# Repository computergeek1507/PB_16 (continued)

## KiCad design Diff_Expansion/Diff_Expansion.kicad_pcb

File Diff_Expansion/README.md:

# Copyright and Disclaimer
Copyright: Scott Hanson

This documentation describes Open Hardware and is licensed under the CERN Open Hardware License Version 2 - Strongly Reciprocal. (CERN-OHL-S)

You may redistribute and modify this documentation under the terms of the CERN OHL-S-v2 (https://ohwr.org/cern_ohl_s_v2.txt). This documentation is distributed WITHOUT ANY EXPRESS OR IMPLIED WARRANTY, INCLUDING OF MERCHANTABILITY, SATISFACTORY QUALITY AND FITNESS FOR A PARTICULAR PURPOSE. Please see the CERN OHL v2-S for applicable conditions

**Under CERN OHL-S-v2, derivative work must be publicly released as defined in subsection 3.3**

# Diff Expansion

The Diff Expansion is a four port Differental Reciever output boardfor the PB16. It works with Smart and Dumb Differental Recievers. All the design files are open source and available on github.

To order, upload the "GERBER-Diff_Expansion.zip" file in the "jlcpcb\gerber" folder to jlcpcb.com.

## [Part BOM](https://github.com/computergeek1507/PB_16/raw/master/Diff_Expansion/Diff_Expansion_BOM.ods)

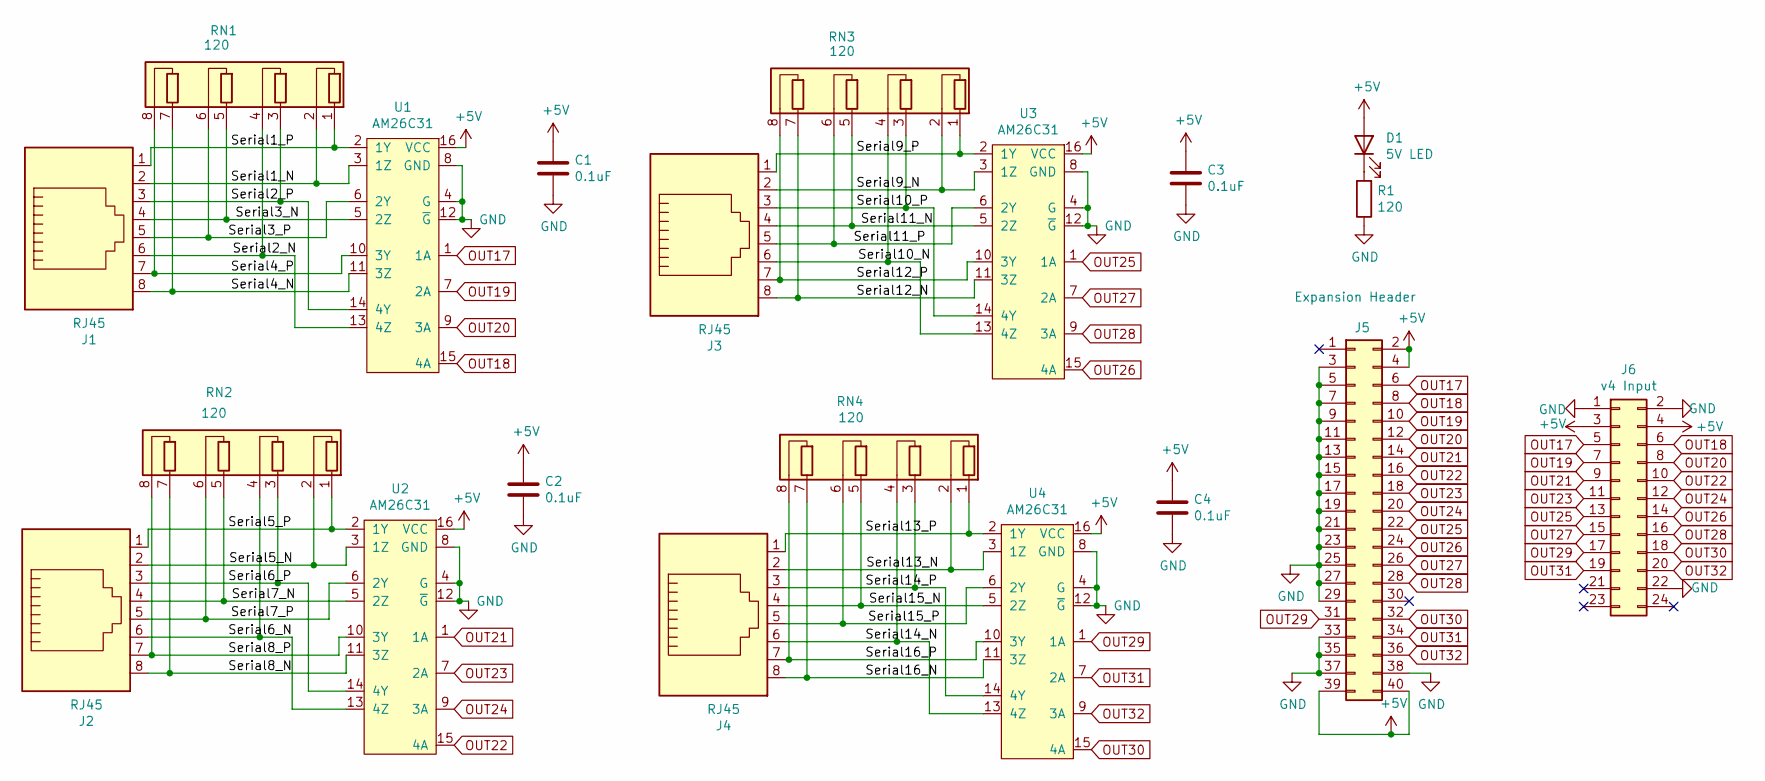
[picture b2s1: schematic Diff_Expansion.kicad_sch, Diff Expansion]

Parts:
C1, C2, C3, C4: 0.1uF; C_Rect_L7.0mm_W2.0mm_P5.00mm; MPN SR215C104KARTR1; Digi-Key_PN 478-7336-1-ND
D1: 5V LED; LED_D3.0mm_Clear; MPN WP3A8GD; Digi-Key_PN 754-1217-ND
J1, J2, J3, J4: RJ45; RJ45_Amphenol_54602-x08_Horizontal; MPN A-2014-2-4-R; Digi-Key_PN AE10392-ND
J5: Expansion Header; IDC-Header_2x20_P2.54mm_Vertical; MPN SBH11-PBPC-D20-ST-BK; Digi-Key_PN S9175-ND
J6: v4 Input; OST_302-S241; MPN 302-S241; Digi-Key_PN ED10525-ND
R1: 120; R_Axial_DIN0207_L6.3mm_D2.5mm_P7.62mm_Horizontal; MPN CF14JT120R; Digi-Key_PN CF14JT120RCT-ND
RN1, RN2, RN3, RN4: 120; R_Array_SIP8; MPN 4608X-102-121LF; Digi-Key_PN 4608X-2-121LF-ND
U1, U2, U3, U4: AM26C31; DIP-16_W7.62mm; MPN AM26C31IN; Farnell 4975637

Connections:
+5V: C1.1, C2.1, C3.1, C4.1, D1.2 (A), J5.2, J5.4, J5.39, J5.40, J6.3, J6.4, U1.16 (VCC), U2.16 (VCC), U3.16 (VCC), U4.16 (VCC)
/Serial1_N: J1.2, RN1.2 (R1.2), U1.3 (1Z)
/Serial1_P: J1.1, RN1.1 (R1.1), U1.2 (1Y)
/Serial2_N: J1.6, RN1.4 (R2.2), U1.13 (4Z)
/Serial2_P: J1.3, RN1.3 (R2.1), U1.14 (4Y)
/Serial3_N: J1.4, RN1.5 (R3.1), U1.5 (2Z)
/Serial3_P: J1.5, RN1.6 (R3.2), U1.6 (2Y)
/Serial4_N: J1.8, RN1.7 (R4.1), U1.11 (3Z)
/Serial4_P: J1.7, RN1.8 (R4.2), U1.10 (3Y)
/Serial5_N: J2.2, RN2.2 (R1.2), U2.3 (1Z)
/Serial5_P: J2.1, RN2.1 (R1.1), U2.2 (1Y)
/Serial6_N: J2.6, RN2.4 (R2.2), U2.13 (4Z)
/Serial6_P: J2.3, RN2.3 (R2.1), U2.14 (4Y)
/Serial7_N: J2.4, RN2.5 (R3.1), U2.5 (2Z)
/Serial7_P: J2.5, RN2.6 (R3.2), U2.6 (2Y)
/Serial8_N: J2.8, RN2.7 (R4.1), U2.11 (3Z)
/Serial8_P: J2.7, RN2.8 (R4.2), U2.10 (3Y)
/Serial9_N: J3.2, RN3.2 (R1.2), U3.3 (1Z)
/Serial9_P: J3.1, RN3.1 (R1.1), U3.2 (1Y)
/Serial10_N: J3.6, RN3.4 (R2.2), U3.13 (4Z)
/Serial10_P: J3.3, RN3.3 (R2.1), U3.14 (4Y)
/Serial11_N: J3.4, RN3.5 (R3.1), U3.5 (2Z)
/Serial11_P: J3.5, RN3.6 (R3.2), U3.6 (2Y)
/Serial12_N: J3.8, RN3.7 (R4.1), U3.11 (3Z)
/Serial12_P: J3.7, RN3.8 (R4.2), U3.10 (3Y)
/Serial13_N: J4.2, RN4.2 (R1.2), U4.3 (1Z)
/Serial13_P: J4.1, RN4.1 (R1.1), U4.2 (1Y)
/Serial14_N: J4.6, RN4.4 (R2.2), U4.13 (4Z)
/Serial14_P: J4.3, RN4.3 (R2.1), U4.14 (4Y)
/Serial15_N: J4.4, RN4.5 (R3.1), U4.5 (2Z)
/Serial15_P: J4.5, RN4.6 (R3.2), U4.6 (2Y)
/Serial16_N: J4.8, RN4.7 (R4.1), U4.11 (3Z)
/Serial16_P: J4.7, RN4.8 (R4.2), U4.10 (3Y)
GND: C1.2, C2.2, C3.2, C4.2, J5.3, J5.5, J5.7, J5.9, J5.11, J5.13, J5.15, J5.17, J5.19, J5.21, J5.23, J5.25, J5.27, J5.29, J5.33, J5.35, J5.37, J5.38, J6.1, J6.2, J6.22, R1.1, U1.4 (G), U1.8 (GND), U1.12 (~G), U2.4 (G), U2.8 (GND), U2.12 (~G), U3.4 (G), U3.8 (GND), U3.12 (~G), U4.4 (G), U4.8 (GND), U4.12 (~G)
unnamed: D1.1 (K), R1.2
OUT17: J5.6, J6.5, U1.1 (1A)
OUT18: J5.8, J6.6, U1.15 (4A)
OUT19: J5.10, J6.7, U1.7 (2A)
OUT20: J5.12, J6.8, U1.9 (3A)
OUT21: J5.14, J6.9, U2.1 (1A)
OUT22: J5.16, J6.10, U2.15 (4A)
OUT23: J5.18, J6.11, U2.7 (2A)
OUT24: J5.20, J6.12, U2.9 (3A)
OUT25: J5.22, J6.13, U3.1 (1A)
OUT26: J5.24, J6.14, U3.15 (4A)
OUT27: J5.26, J6.15, U3.7 (2A)
OUT28: J5.28, J6.16, U3.9 (3A)
OUT29: J5.31, J6.17, U4.1 (1A)
OUT30: J5.32, J6.18, U4.15 (4A)
OUT31: J5.34, J6.19, U4.7 (2A)
OUT32: J5.36, J6.20, U4.9 (3A)

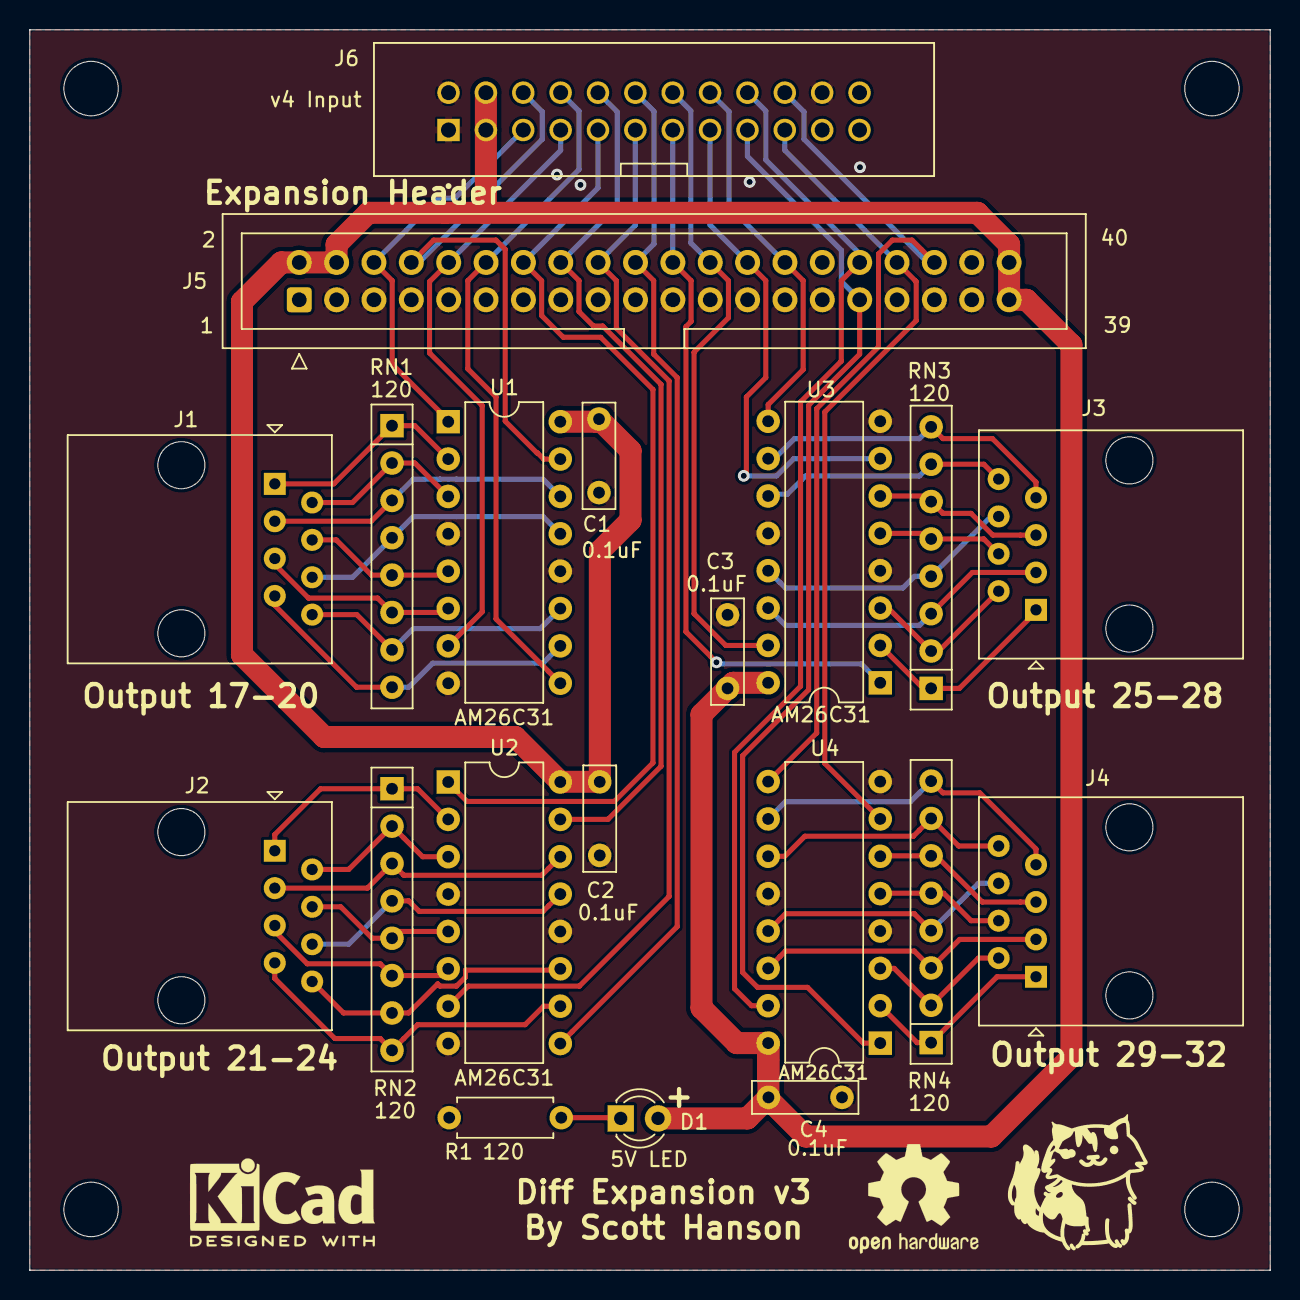
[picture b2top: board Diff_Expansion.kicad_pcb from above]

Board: 2 copper layers, 84.3 x 84.3 mm, 20 parts (0 on the bottom side), 51 nets.

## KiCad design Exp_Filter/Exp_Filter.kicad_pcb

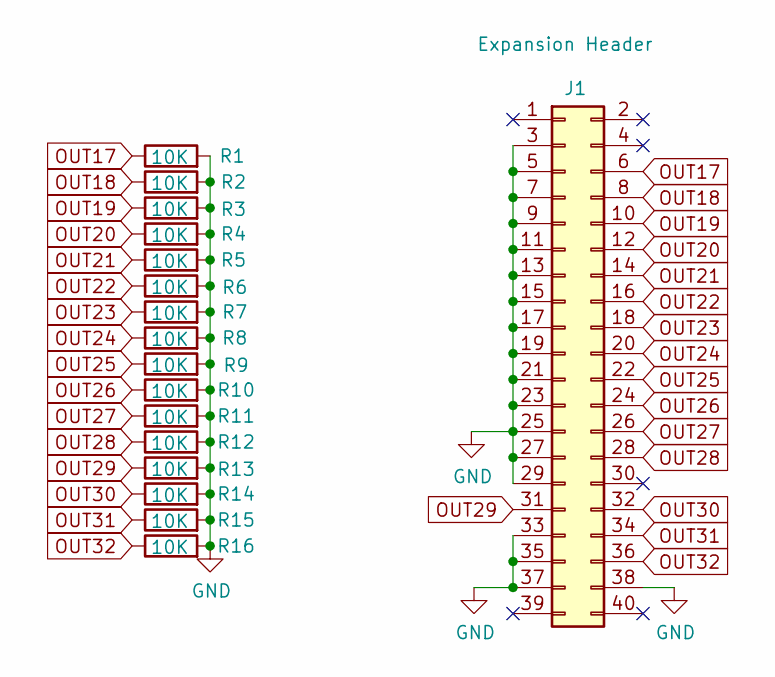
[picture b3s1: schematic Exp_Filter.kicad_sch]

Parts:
J1: Expansion Header; PinSocket_2x20_P2.54mm_Vertical; MPN SFH11-PBPC-D20-ST-BK; Digi-Key_PN S9200-ND
R1, R2, R3, R4, R5, R6, R7, R8, R9, R10, R11, R12, R13, R14, R15, R16: 10K; R_0603_1608Metric_Pad0.98x0.95mm_HandSolder; MPN RC0603FR-0710KL; Digi-Key_PN 311-10.0KHRCT-ND

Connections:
GND: J1.3, J1.5, J1.7, J1.9, J1.11, J1.13, J1.15, J1.17, J1.19, J1.21, J1.23, J1.25, J1.27, J1.29, J1.33, J1.35, J1.37, J1.38, R1.2, R2.2, R3.2, R4.2, R5.2, R6.2, R7.2, R8.2, R9.2, R10.2, R11.2, R12.2, R13.2, R14.2, R15.2, R16.2
OUT17: J1.6, R1.1
OUT18: J1.8, R2.1
OUT19: J1.10, R3.1
OUT20: J1.12, R4.1
OUT21: J1.14, R5.1
OUT22: J1.16, R6.1
OUT23: J1.18, R7.1
OUT24: J1.20, R8.1
OUT25: J1.22, R9.1
OUT26: J1.24, R10.1
OUT27: J1.26, R11.1
OUT28: J1.28, R12.1
OUT29: J1.31, R13.1
OUT30: J1.32, R14.1
OUT31: J1.34, R15.1
OUT32: J1.36, R16.1

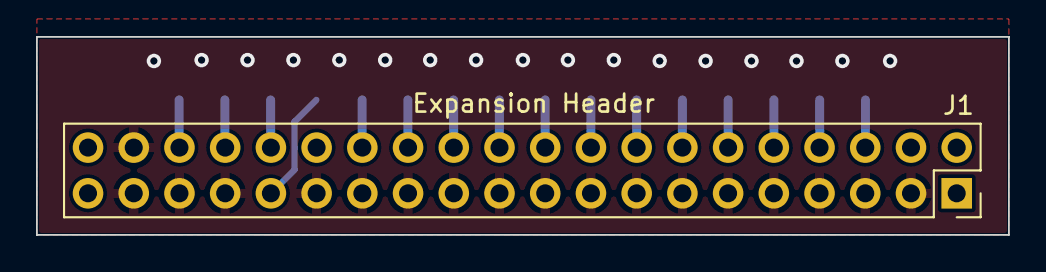
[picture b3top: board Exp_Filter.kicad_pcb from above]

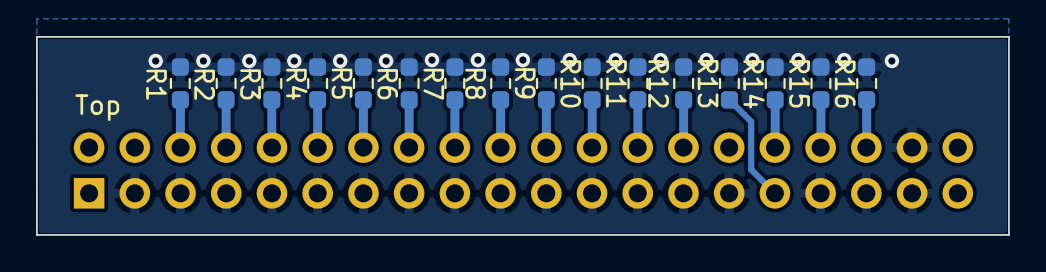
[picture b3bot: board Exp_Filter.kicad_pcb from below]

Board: 2 copper layers, 54.0 x 11.0 mm, 17 parts (16 on the bottom side), 17 nets.

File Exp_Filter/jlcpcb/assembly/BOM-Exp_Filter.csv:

Comment,Designator,Footprint,LCSC
10K,"R1,R10,R11,R12,R13,R14,R15,R16,R2,R3,R4,R5,R6,R7,R8,R9",R_0603_1608Metric_Pad0.98x0.95mm_HandSolder,C25804
Expansion Header,J1,PinSocket_2x20_P2.54mm_Vertical,C50982

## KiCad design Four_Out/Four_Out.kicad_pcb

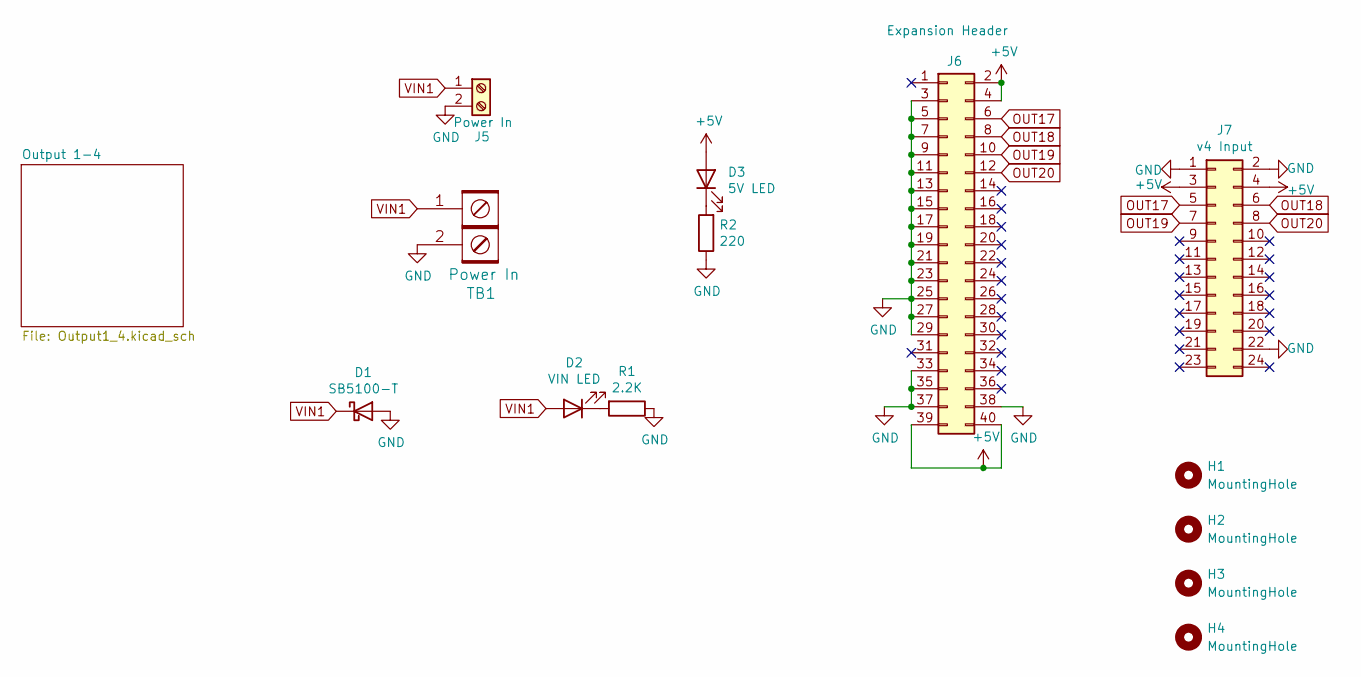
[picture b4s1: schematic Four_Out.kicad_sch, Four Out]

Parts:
D1: SB5100-T; D_DO-201AD_P12.70mm_Horizontal; MPN SB5100-T; Digi-Key_PN SB5100DICT-ND
D2: VIN LED; LED_D3.0mm_Clear; MPN WP3A8GD; Digi-Key_PN 754-1217-ND
D3: 5V LED; LED_D3.0mm_Clear; MPN WP3A8GD; Digi-Key_PN 754-1217-ND
H1, H2, H3, H4: MountingHole; MountingHole_3.7mm
J5: Power In; TerminalBlock_MetzConnect_Type701_RT11L02HGLU_1x02_P6.35mm_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; Digi-Key_PN ED2675-ND
J6: Expansion Header; IDC-Header_2x20_P2.54mm_Vertical; MPN SBH11-PBPC-D20-ST-BK; Digi-Key_PN S9175-ND
J7: v4 Input; OST_302-S241; MPN 302-S241; Digi-Key_PN ED10525-ND
R1: 2.2K; R_Axial_DIN0207_L6.3mm_D2.5mm_P7.62mm_Horizontal; MPN CF14JT1K00; Digi-Key_PN CF14JT1K00CT-ND
R2: 220; R_Axial_DIN0207_L6.3mm_D2.5mm_P7.62mm_Horizontal; MPN CF14JT120R; Digi-Key_PN CF14JT120RCT-ND
TB1: Power In; BARRIER_BLOCK_1ROW_2POS

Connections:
+5V: D3.2 (A), J6.2, J6.4, J6.39, J6.40, J7.3, J7.4; also elsewhere on the board
GND: D1.2 (A), J5.2, J6.3, J6.5, J6.7, J6.9, J6.11, J6.13, J6.15, J6.17, J6.19, J6.21, J6.23, J6.25, J6.27, J6.29, J6.33, J6.35, J6.37, J6.38, J7.1, J7.2, J7.22, R1.1, R2.1, TB1.2; also elsewhere on the board
unnamed: D2.1 (K), R1.2
unnamed: D3.1 (K), R2.2
OUT17: J6.6, J7.5; also elsewhere on the board
OUT18: J6.8, J7.6; also elsewhere on the board
OUT19: J6.10, J7.7; also elsewhere on the board
OUT20: J6.12, J7.8; also elsewhere on the board
VIN1: D1.1 (K), D2.2 (A), J5.1, TB1.1; also elsewhere on the board

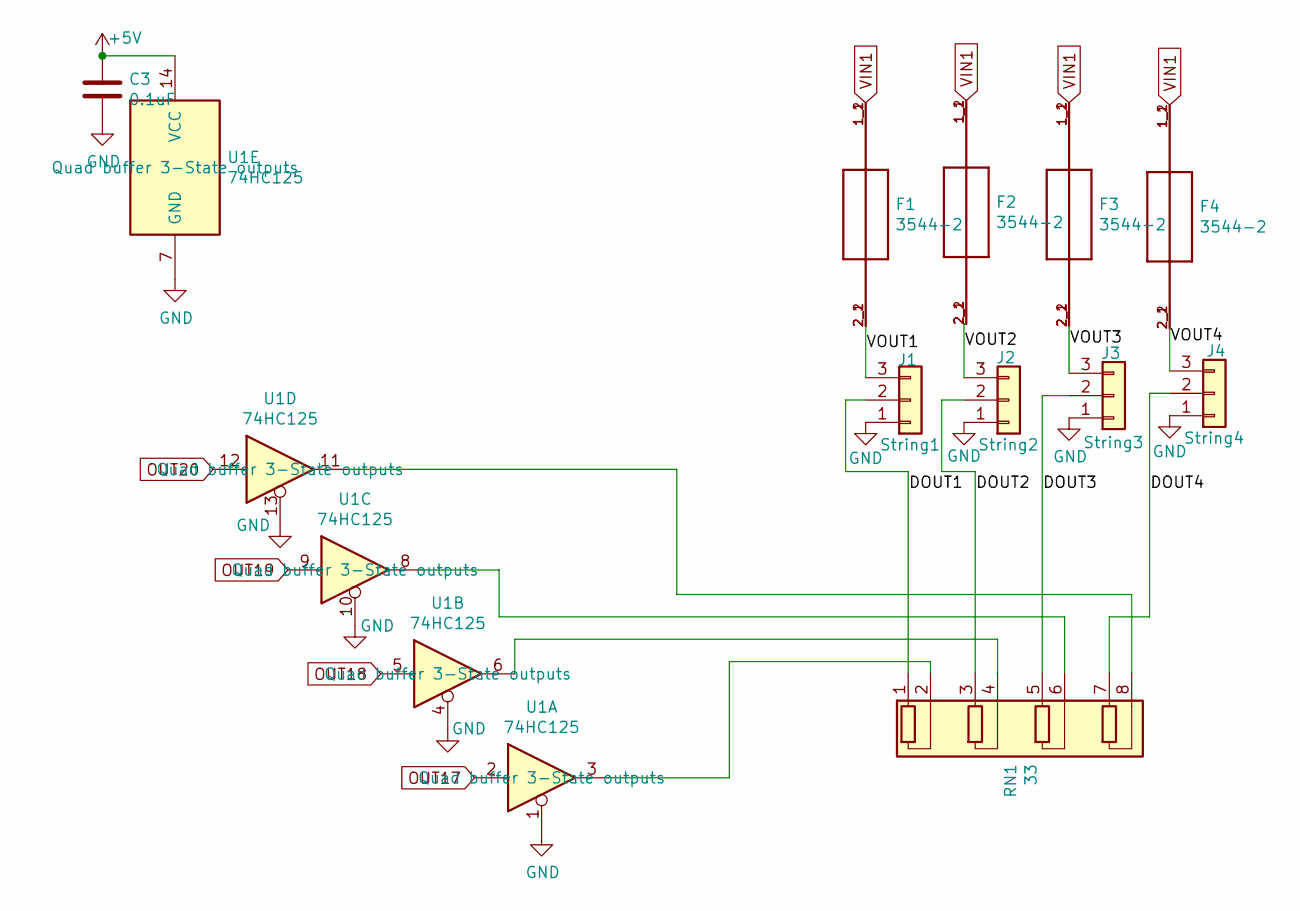
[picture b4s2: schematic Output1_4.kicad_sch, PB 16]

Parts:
C3: 0.1uF; C_Rect_L7.0mm_W2.0mm_P5.00mm; MPN SR215C104KARTR1; Digi-Key_PN 478-7336-1-ND
F1, F2, F3, F4: 3544-2; FUSE_3544-2; MPN 3544-2; Digi-Key_PN 36-3544-2-ND
J1: String1; PhoenixContact_MCV_1,5_3-G-3.5_1x03_P3.50mm_Vertical; MPN 1843619/OSTTJ0311530; Digi-Key_PN 277-5737-ND/ED10555-ND
J2: String2; PhoenixContact_MCV_1,5_3-G-3.5_1x03_P3.50mm_Vertical; MPN 1843619/OSTTJ0311530; Digi-Key_PN 277-5737-ND/ED10555-ND
J3: String3; PhoenixContact_MCV_1,5_3-G-3.5_1x03_P3.50mm_Vertical; MPN 1843619/OSTTJ0311530; Digi-Key_PN 277-5737-ND/ED10555-ND
J4: String4; PhoenixContact_MCV_1,5_3-G-3.5_1x03_P3.50mm_Vertical; MPN 1843619/OSTTJ0311530; Digi-Key_PN 277-5737-ND/ED10555-ND
RN1: 33; R_Array_SIP8; MPN 4608X-102-330LF; Digi-Key_PN 4608X-2-330LF-ND
U1: 74HC125; DIP-14_W7.62mm_LongPads; MPN SN74AHC125N; Digi-Key_PN 296-4531-5-ND

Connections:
+5V: C3.1, U1.14 (VCC); also elsewhere on the board
/Output 1-4/DOUT1: J1.2, RN1.1 (R1.1)
/Output 1-4/DOUT2: J2.2, RN1.3 (R2.1)
/Output 1-4/DOUT3: J3.2, RN1.5 (R3.1)
/Output 1-4/DOUT4: J4.2, RN1.7 (R4.1)
/Output 1-4/VOUT1: F1.2_1 (2), F1.2_2 (2), J1.3
/Output 1-4/VOUT2: F2.2_1 (2), F2.2_2 (2), J2.3
/Output 1-4/VOUT3: F3.2_1 (2), F3.2_2 (2), J3.3
/Output 1-4/VOUT4: F4.2_1 (2), F4.2_2 (2), J4.3
GND: C3.2, J1.1, J2.1, J3.1, J4.1, U1.1, U1.4, U1.7 (GND), U1.10, U1.13; also elsewhere on the board
unnamed: RN1.2 (R1.2), U1.3
unnamed: RN1.4 (R2.2), U1.6
unnamed: RN1.6 (R3.2), U1.8
unnamed: RN1.8 (R4.2), U1.11
OUT17: U1.2; also elsewhere on the board
OUT18: U1.5; also elsewhere on the board
OUT19: U1.9; also elsewhere on the board
OUT20: U1.12; also elsewhere on the board
VIN1: F1.1_1 (1), F1.1_2 (1), F2.1_1 (1), F2.1_2 (1), F3.1_1 (1), F3.1_2 (1), F4.1_1 (1), F4.1_2 (1); also elsewhere on the board

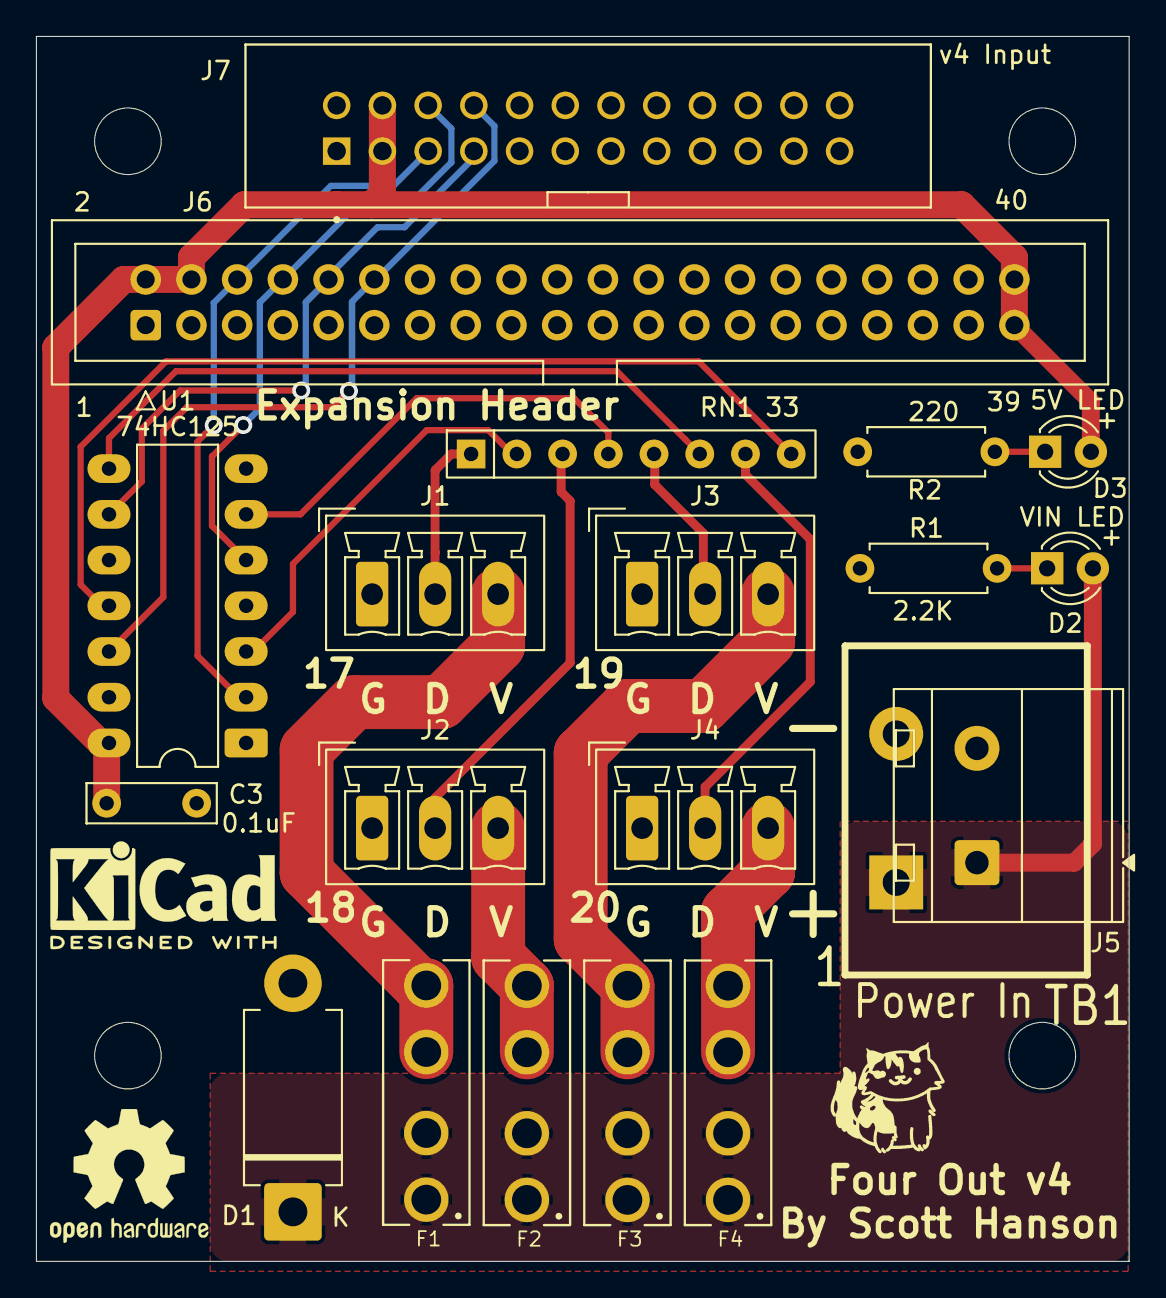
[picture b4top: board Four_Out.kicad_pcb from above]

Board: 2 copper layers, 60.7 x 68.1 mm, 24 parts (0 on the bottom side), 21 nets.

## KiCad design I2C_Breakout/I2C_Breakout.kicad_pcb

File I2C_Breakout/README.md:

# Copyright and Disclaimer
Copyright: Scott Hanson

This documentation describes Open Hardware and is licensed under the CERN Open Hardware License Version 2 - Strongly Reciprocal. (CERN-OHL-S)

You may redistribute and modify this documentation under the terms of the CERN OHL-S-v2 (https://ohwr.org/cern_ohl_s_v2.txt). This documentation is distributed WITHOUT ANY EXPRESS OR IMPLIED WARRANTY, INCLUDING OF MERCHANTABILITY, SATISFACTORY QUALITY AND FITNESS FOR A PARTICULAR PURPOSE. Please see the CERN OHL v2-S for applicable conditions

**Under CERN OHL-S-v2, derivative work must be publicly released as defined in subsection 3.3**

# PB 16 1.0e EEPROM Breakout

The PB16 EEPROM Breakout adds an EEPROM ship to the older PB16 version 1.0e controllers.  All the design files are open source and available on github.

## [Part BOM](https://github.com/computergeek1507/PB_16/raw/master/I2C_Breakout/I2C_Breakout_BOM.ods)

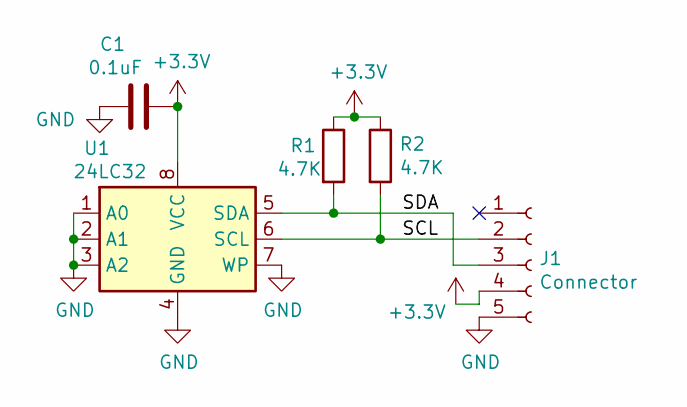
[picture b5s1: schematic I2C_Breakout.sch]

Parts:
C1: 0.1uF; C_Rect_L7.0mm_W2.0mm_P5.00mm
J1: Connector; PinSocket_1x05_P2.54mm_Vertical
R1, R2: 4.7K; R_Axial_DIN0207_L6.3mm_D2.5mm_P7.62mm_Horizontal
U1: 24LC32; DIP-8_W7.62mm

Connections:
+3V3: C1.1, J1.4, R1.1, R2.1, U1.8 (VCC)
/SCL: J1.2, R2.2, U1.6 (SCL)
/SDA: J1.3, R1.2, U1.5 (SDA)
GND: C1.2, J1.5, U1.1 (A0), U1.2 (A1), U1.3 (A2), U1.4 (GND), U1.7 (WP)

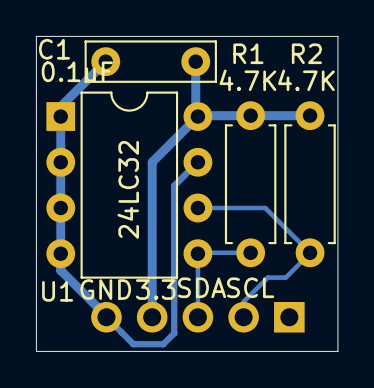
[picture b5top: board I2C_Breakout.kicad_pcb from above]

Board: 2 copper layers, 16.8 x 17.5 mm, 5 parts (1 on the bottom side), 4 nets.

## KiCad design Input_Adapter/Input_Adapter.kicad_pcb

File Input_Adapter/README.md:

# Copyright and Disclaimer
Copyright: Scott Hanson

This documentation describes Open Hardware and is licensed under the CERN Open Hardware License Version 2 - Strongly Reciprocal. (CERN-OHL-S)

You may redistribute and modify this documentation under the terms of the CERN OHL-S-v2 (https://ohwr.org/cern_ohl_s_v2.txt). This documentation is distributed WITHOUT ANY EXPRESS OR IMPLIED WARRANTY, INCLUDING OF MERCHANTABILITY, SATISFACTORY QUALITY AND FITNESS FOR A PARTICULAR PURPOSE. Please see the CERN OHL v2-S for applicable conditions

**Under CERN OHL-S-v2, derivative work must be publicly released as defined in subsection 3.3**

# Input2Expansion

The Input2Expansion board is an adapter to use the Experience Lights Input Extender Kit with Expansion Port on a Kulp or PB16 Pixel Controller.  All the design files are open source and available on github.

# Configuration

Experience Lights Input Extender Pin to Controller GPIO Map

|Controller  |Button 1 |Button 2 |Button 3 |Button 4 |Button 5 |Button 6 |
|------------|---------|---------|---------|---------|---------|---------|
|Pi GPIO     |GPIO 17  |GPIO 18  |GPIO 27  |GPIO 22  |GPIO 23  |GPIO 24  |
|Expansion   |Output 15|Output 14|Output 13|Output 12|Output 11|Output 10|
|PB16v1 GPIO |P2-03    |P2-05    |P2-07    |P1-17    |P2-20    |P2-19    |
|PB16v2 GPIO |P2-25    |P2-03    |P2-17    |P2-11    |P2-10    |P1-12    |
|K16A-B GPIO |P8-33    |P8-31    |P8-32    |P9-19    |P8-14    |P8-17    |
|K8-B GPIO   |P8-12    |P8-11    |P9-23    |P9-15    |P9-16    |P9-14    |
|K8-PB GPIO  |P2-05    |P2-07    |P2-09    |P2-17    |P1-04    |P1-06    |
|BBB16v2 GPIO|P8-35    |P8-33    |P8-31    |P8-30    |P2-29    |P8-28    |
|F8-PBv2 GPIO|P2-05    |P2-07    |P2-09    |P2-11    |P2-17    |P2-20    |

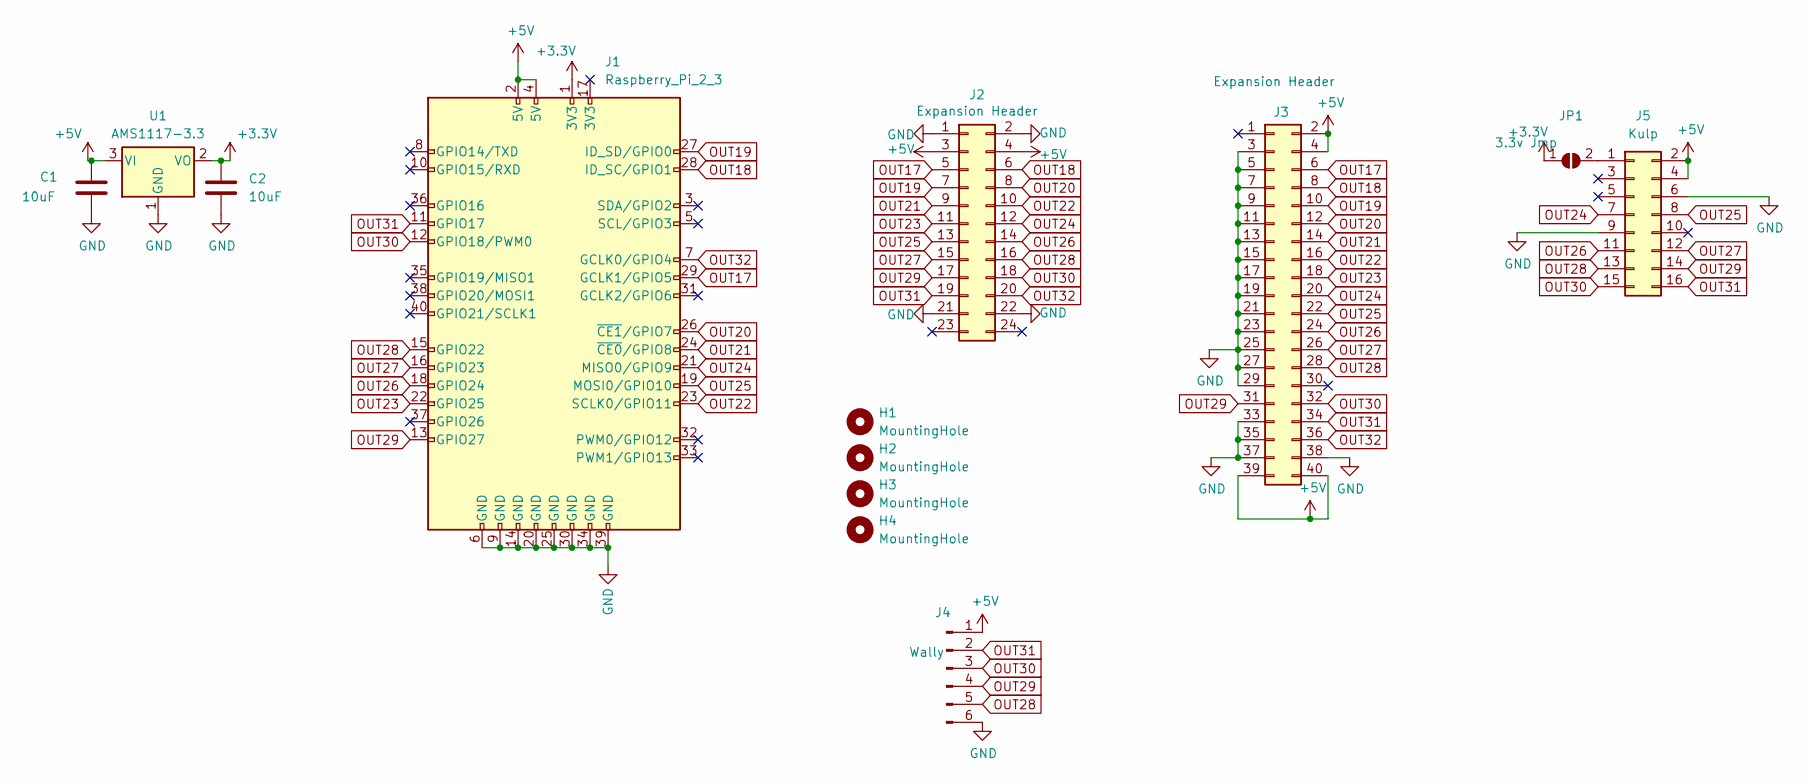
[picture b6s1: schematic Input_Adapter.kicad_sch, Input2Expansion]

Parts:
C1, C2: 10uF; C_0805_2012Metric_Pad1.18x1.45mm_HandSolder; LCSC C15850
H1, H2, H3, H4: MountingHole; MountingHole_3.2mm_M3
J1: Raspberry_Pi_2_3; Raspberry_Pi_Hat_Socketed_THT_FaceDown_MountingHoles; LCSC C124383
J2: Expansion Header; OST_302-S241; MPN 302-S241; Digi-Key_PN ED10525-ND
J3: Expansion Header; IDC-Header_2x20_P2.54mm_Vertical; MPN SBH11-PBPC-D20-ST-BK; Digi-Key_PN S9175-ND
J4: Wally; JST_XH_B6B-XH-A_1x06_P2.50mm_Vertical; LCSC C144397
J5: Kulp; PinHeader_2x08_P2.54mm_Vertical; LCSC C706898
JP1: 3.3v Jmp; SolderJumper-2_P1.3mm_Open_RoundedPad1.0x1.5mm
U1: AMS1117-3.3; SOT-223-3_TabPin2; LCSC C6186

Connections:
+3V3: C2.1, J1.1 (3V3), JP1.1 (A), U1.2 (VO)
+5V: C1.1, J1.2 (5V), J1.4 (5V), J2.3, J2.4, J3.2, J3.4, J3.39, J3.40, J4.1, J5.2, J5.4, U1.3 (VI)
GND: C1.2, C2.2, J1.6 (GND), J1.9 (GND), J1.14 (GND), J1.20 (GND), J1.25 (GND), J1.30 (GND), J1.34 (GND), J1.39 (GND), J2.1, J2.2, J2.21, J2.22, J3.3, J3.5, J3.7, J3.9, J3.11, J3.13, J3.15, J3.17, J3.19, J3.21, J3.23, J3.25, J3.27, J3.29, J3.33, J3.35, J3.37, J3.38, J4.6, J5.6, J5.9, U1.1 (GND)
unnamed: J5.1, JP1.2 (B)
OUT17: J1.29 (GCLK1/GPIO5), J2.5, J3.6
OUT18: J1.28 (ID_SC/GPIO1), J2.6, J3.8
OUT19: J1.27 (ID_SD/GPIO0), J2.7, J3.10
OUT20: J1.26 (~CE1/GPIO7), J2.8, J3.12
OUT21: J1.24 (~CE0/GPIO8), J2.9, J3.14
OUT22: J1.23 (SCLK0/GPIO11), J2.10, J3.16
OUT23: J1.22 (GPIO25), J2.11, J3.18
OUT24: J1.21 (MISO0/GPIO9), J2.12, J3.20, J5.7
OUT25: J1.19 (MOSI0/GPIO10), J2.13, J3.22, J5.8
OUT26: J1.18 (GPIO24), J2.14, J3.24, J5.11
OUT27: J1.16 (GPIO23), J2.15, J3.26, J5.12
OUT28: J1.15 (GPIO22), J2.16, J3.28, J4.5, J5.13
OUT29: J1.13 (GPIO27), J2.17, J3.31, J4.4, J5.14
OUT30: J1.12 (GPIO18/PWM0), J2.18, J3.32, J4.3, J5.15
OUT31: J1.11 (GPIO17), J2.19, J3.34, J4.2, J5.16
OUT32: J1.7 (GCLK0/GPIO4), J2.20, J3.36

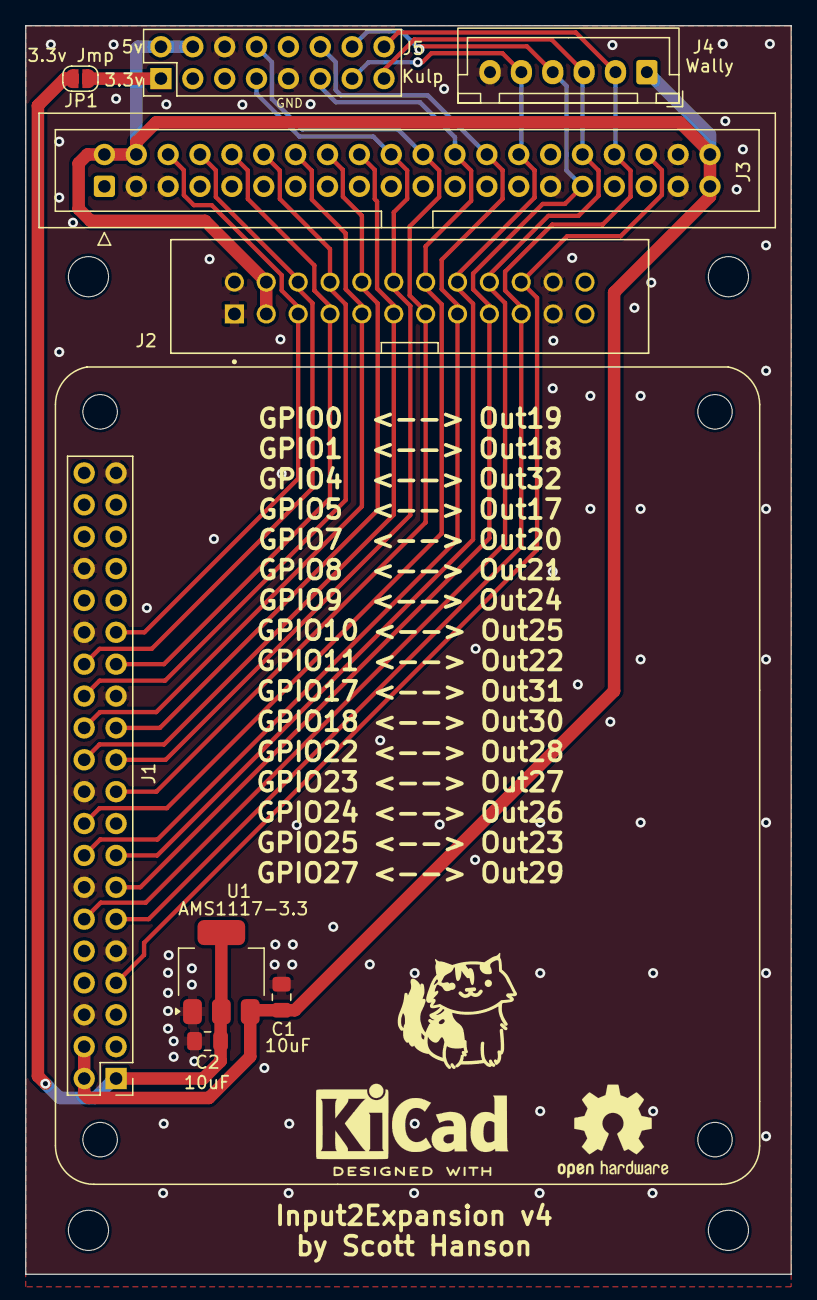
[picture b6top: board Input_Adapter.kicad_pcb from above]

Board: 2 copper layers, 61.0 x 99.5 mm, 13 parts (1 on the bottom side), 20 nets.

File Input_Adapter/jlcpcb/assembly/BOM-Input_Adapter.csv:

Comment,Designator,Footprint,LCSC
Raspberry_Pi_2_3,J1,Raspberry_Pi_Hat_Socketed_THT_FaceDown_MountingHoles,C124383
Wally,J4,JST_XH_B6B-XH-A_1x06_P2.50mm_Vertical,C144397
10uF,"C1,C2",C_0805_2012Metric_Pad1.18x1.45mm_HandSolder,C15850
Expansion Header,J2,OST_302-S241,C221083
Expansion Header,J3,IDC-Header_2x20_P2.54mm_Vertical,C358750
AMS1117-3.3,U1,SOT-223-3_TabPin2,C6186
Kulp,J5,PinHeader_2x08_P2.54mm_Vertical,C706898

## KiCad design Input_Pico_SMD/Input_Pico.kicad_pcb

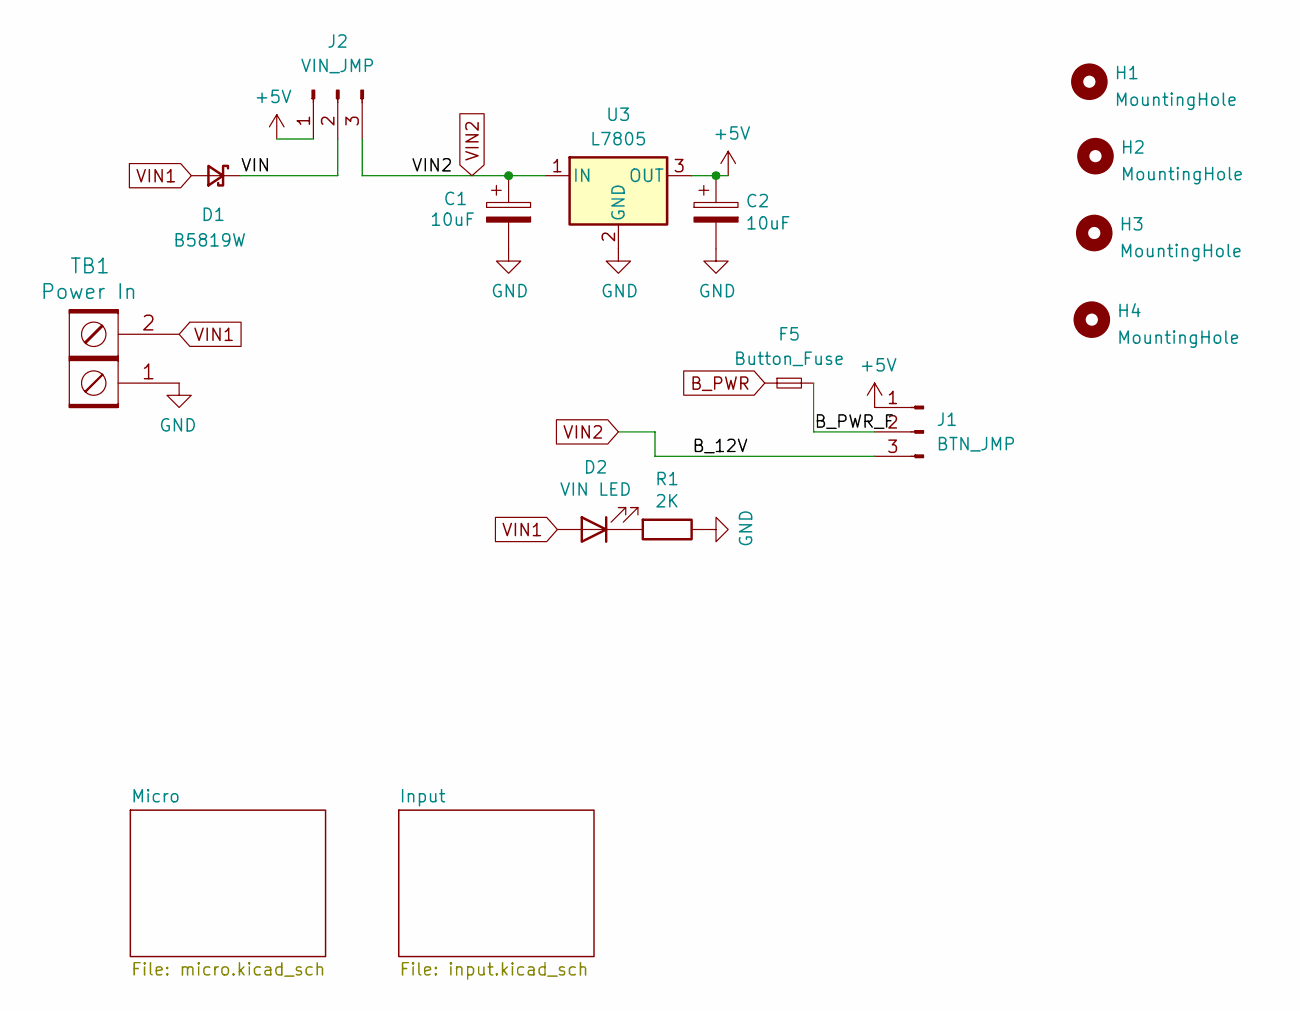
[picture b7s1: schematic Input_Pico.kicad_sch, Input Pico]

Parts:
C1, C2: 10uF; C_0805_2012Metric; MPN GRM21BR61E106KA73L; Digi-Key_PN 490-5523-1-ND
D1: B5819W; D_SOD-123; MPN B5819W-TP; LCSC_PN C8598
D2: VIN LED; LED_0603_1608Metric; MPN 150080RS75000; Digi-Key_PN 732-4984-1-ND
F5: Button_Fuse; Fuse_0805_2012Metric; LCSC C261938
H1, H2, H3, H4: MountingHole; MountingHole_3.7mm
J1: BTN_JMP; PinHeader_1x03_P2.54mm_Vertical
J2: VIN_JMP; PinHeader_1x03_P2.54mm_Vertical
R1: 2K; R_0603_1608Metric; MPN RC0603FR-071KL; Digi-Key_PN 311-1.00KHRCT-ND
TB1: Power In; TerminalBlock_Phoenix_MKDS-1,5-2-5.08_1x02_P5.08mm_Horizont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; MPN 4DB-P108-02; Digi-Key_PN A98472-ND
U3: L7805; TO-252-2; LCSC_PN C58069

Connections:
+5V: C2.1, J1.1, J2.1, U3.3 (OUT); also elsewhere on the board
/B_PWR_F: F5.2, J1.2
/VIN: D1.1 (K), J2.2
B_PWR: F5.1; also elsewhere on the board
GND: C1.2, C2.2, R1.1, TB1.1, U3.2 (GND); also elsewhere on the board
unnamed: D2.1 (K), R1.2
VIN1: D1.2 (A), D2.2 (A), TB1.2
VIN2: C1.1, J1.3, J2.3, U3.1 (IN)

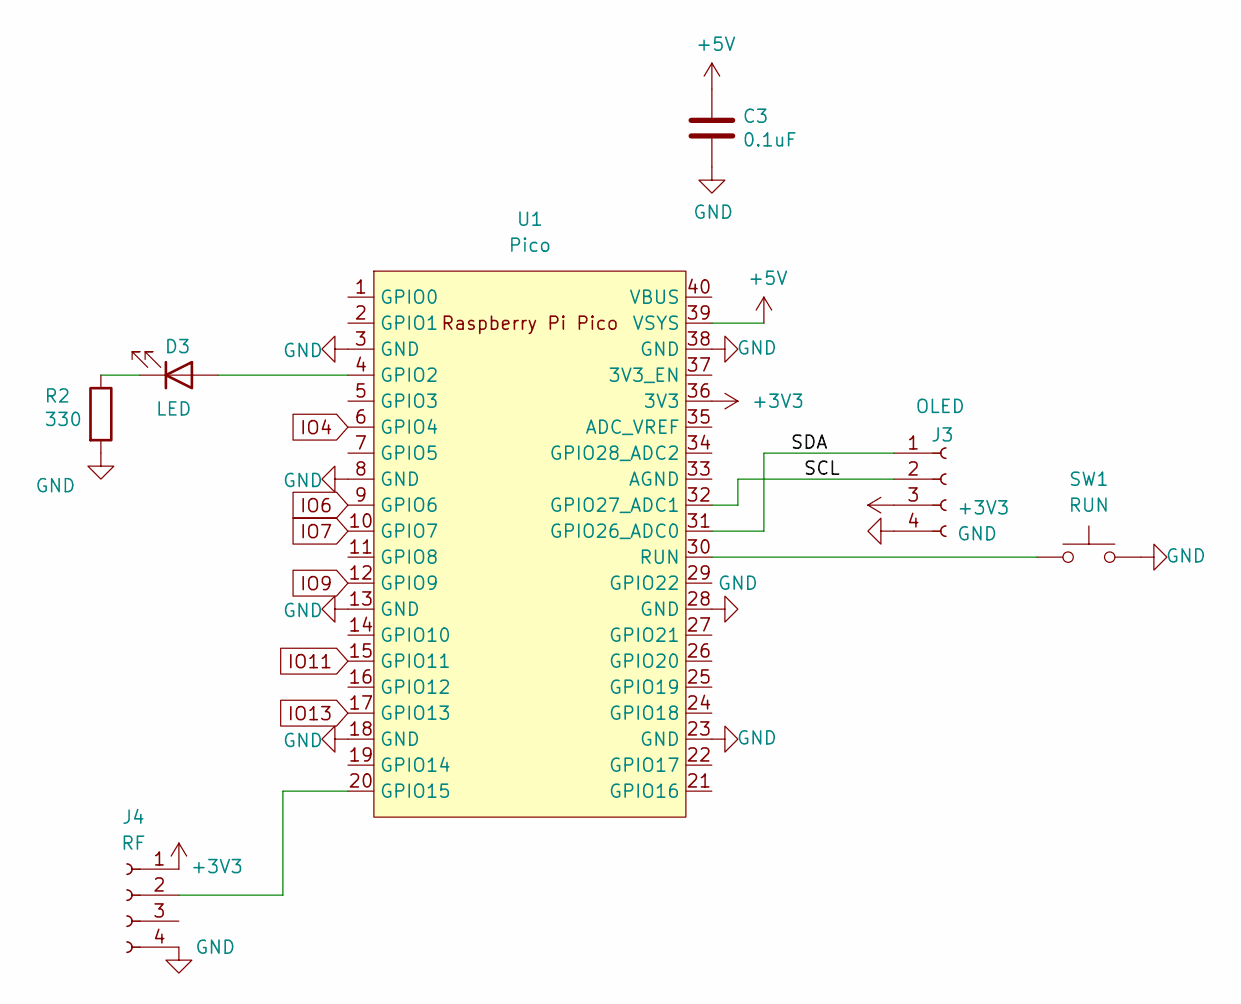
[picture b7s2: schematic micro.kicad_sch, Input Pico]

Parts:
C3: 0.1uF; C_0603_1608Metric; MPN CL10B104KB8NNWC; Digi-Key_PN 1276-1935-2-ND
D3: LED; LED_0603_1608Metric; MPN 150080RS75000; Digi-Key_PN 732-4984-1-ND
J3: OLED; OLED-SSD1306-128X64-I2C-THT; MPN PPTC041LFBN-RC; Digi-Key_PN S7002-ND
J4: RF; PinSocket_1x04_P2.54mm_Vertical
R2: 330; R_0603_1608Metric; MPN RMCF0603FT220R; Digi-Key_PN RMCF0603FT220RTR-ND
SW1: RUN; SW_PUSH_6mm; MPN PTS645SL50SMTR92 LFS; Digi-Key_PN CKN9088CT-ND
U1: Pico; RPi_Pico_W5500_SMD_TH

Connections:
+3V3: J3.3, J4.1, U1.36 (3V3); also elsewhere on the board
+5V: C3.1, U1.39 (VSYS); also elsewhere on the board
/Micro/SCL: J3.2, U1.32 (GPIO27_ADC1)
/Micro/SDA: J3.1, U1.31 (GPIO26_ADC0)
GND: C3.2, J3.4, J4.4, R2.2, SW1.2, U1.3 (GND), U1.8 (GND), U1.13 (GND), U1.18 (GND), U1.23 (GND), U1.28 (GND), U1.38 (GND); also elsewhere on the board
IO4: U1.6 (GPIO4); also elsewhere on the board
IO6: U1.9 (GPIO6); also elsewhere on the board
IO7: U1.10 (GPIO7); also elsewhere on the board
IO9: U1.12 (GPIO9); also elsewhere on the board
IO11: U1.15 (GPIO11); also elsewhere on the board
IO13: U1.17 (GPIO13); also elsewhere on the board
unnamed: D3.2 (A), U1.4 (GPIO2)
unnamed: D3.1 (K), R2.1
unnamed: J4.2, U1.20 (GPIO15)
unnamed: SW1.1, U1.30 (RUN)
